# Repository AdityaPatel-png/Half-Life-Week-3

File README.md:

# Half-Life-Week-3
Miniature synthesizer project
For this project, I have decided to make a miniature synthesizer powered by a Raspberry Pi Zero.
It will have 13 keys (1 octave) and a dial that will allow to change between 4 octaves.
The code will be done in arduino and the design in Kicad.
I am not a musician and therefore will use a friend to test its functionality in the build week.

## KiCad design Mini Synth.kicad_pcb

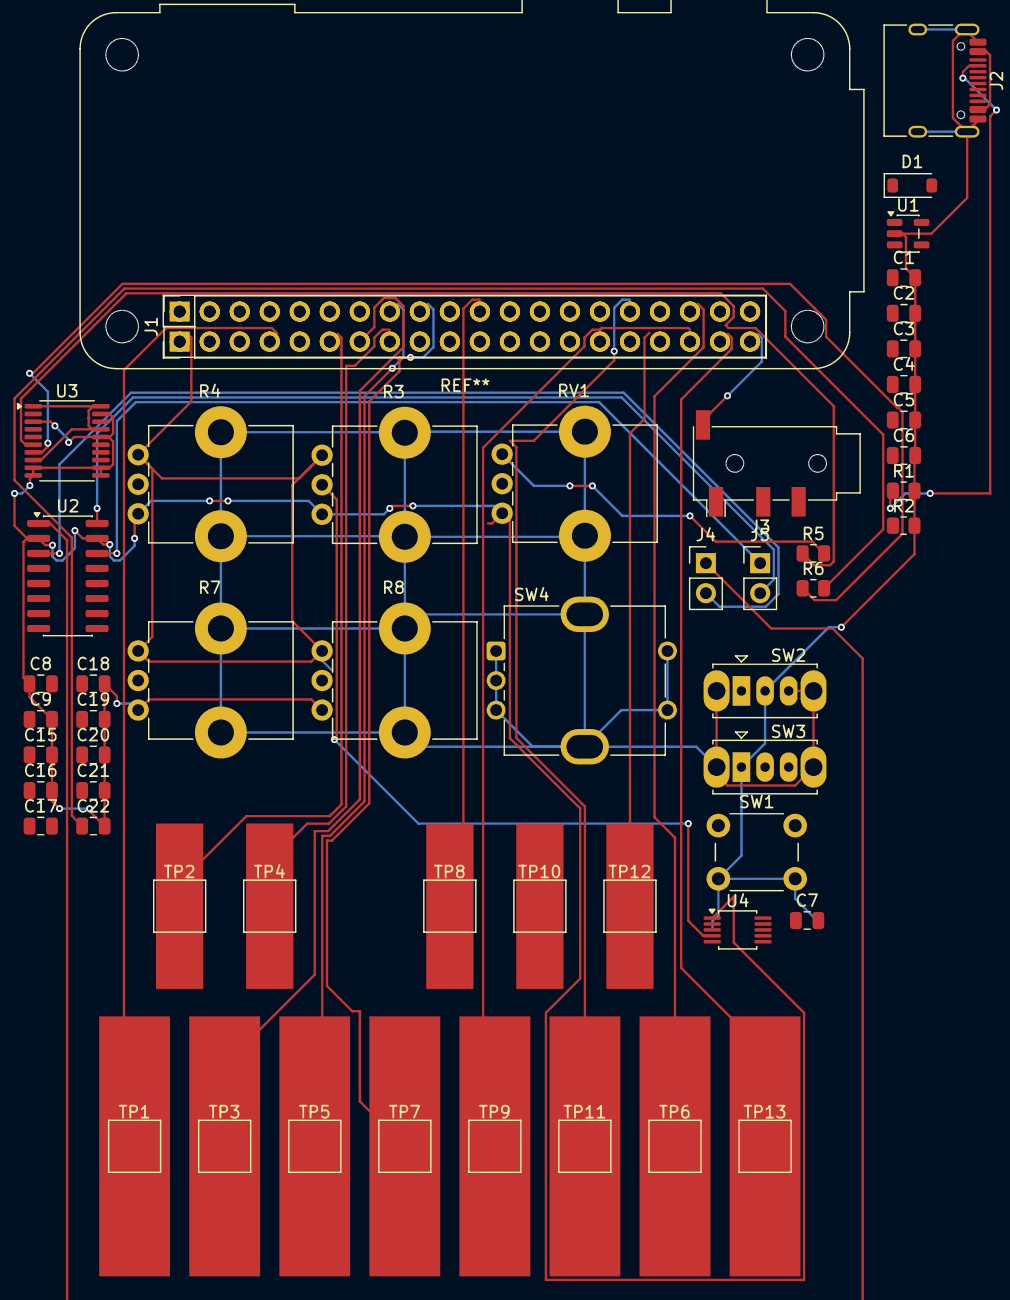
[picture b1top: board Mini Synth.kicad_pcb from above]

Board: 2 copper layers, 53 parts (0 on the bottom side), 47 nets.

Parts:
C1: 10µF; C_0805_2012Metric
C2, C3, C17, C19, C20: 1.0µF; C_0805_2012Metric
C4, C5, C6, C7, C15, C16, C18: 0.1µF; C_0805_2012Metric
C8, C9: C; C_0805_2012Metric
C21, C22: 2.2nF; C_0805_2012Metric
D1: D_Schottky; D_SOD-123
J1: Conn_02x20_Odd_Even; PinHeader_2x20_P2.54mm_Vertical
J2: USB_C_Receptacle_USB2.0_16P; USB_C_Receptacle_HRO_TYPE-C-31-M-12
J3: AudioJack3_Switch; Jack_3.5mm_PJ320D_Horizontal
J4, J5: Conn_01x02_Socket; PinHeader_1x02_P2.54mm_Vertical
R1, R2: 5.1K; R_0805_2012Metric
R3, R4, R7, R8: Potentiometer; Potentiometer_Bourns_PTV09A-1_Single_Vertical
R5, R6: 470; R_0805_2012Metric
RV1: R_Potentiometer_Dual; Potentiometer_Bourns_PTV09A-1_Single_Vertical
SW1: SW_Push; SW_PUSH_6mm
SW2: SW_SPST; SW_Slide_SPDT_Straight_CK_OS102011MS2Q
SW3: SW_Slide_DPDT; SW_Slide_SPDT_Straight_CK_OS102011MS2Q
SW4: SW_Rotary_1x4_MP; RotaryEncoder_Bourns_Vertical_PEC12R-3x17F-Sxxxx
TP1: KEY_C; TestPoint_Pad_4.0x4.0mm
TP2: KEY_CSHARP; TestPoint_Pad_4.0x4.0mm
TP3: KEY_D; TestPoint_Pad_4.0x4.0mm
TP4: KEY_DSHARP; TestPoint_Pad_4.0x4.0mm
TP5: KEY_E; TestPoint_Pad_4.0x4.0mm
TP6: KEY_B; TestPoint_Pad_4.0x4.0mm
TP7: KEY_F; TestPoint_Pad_4.0x4.0mm
TP8: KEY_FSHARP; TestPoint_Pad_4.0x4.0mm
TP9: KEY_G; TestPoint_Pad_4.0x4.0mm
TP10: KEY_GSHARP; TestPoint_Pad_4.0x4.0mm
TP11: KEY_A; TestPoint_Pad_4.0x4.0mm
TP12: KEY_ASHARP; TestPoint_Pad_4.0x4.0mm
TP13: KEY_HIGH_C; TestPoint_Pad_4.0x4.0mm
U1: TLV75533PDBV; SOT-23-5
U2: PAM8403D; SOIC-16_3.9x9.9mm_P1.27mm
U3: PCM5102A; TSSOP-20_4.4x6.5mm_P0.65mm
U4: ADS1115IDGS; TSSOP-10_3x3mm_P0.5mm

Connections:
/3V3_ANA: C3.1, C5.1
/5V_SYS: C1.1, C2.1, C4.1, C6.1, D1.2 (A), U1.1 (IN), U1.3 (EN)
/Audio DAC/3V3_ANA: C15.1, C16.1, C18.1, U1.5 (OUT), U3.1 (CPVDD), U3.8 (AVDD), U3.17 (XSMT), U3.20 (DVDD)
/Audio DAC/5V_SYS: C9.1, J1.2, U2.4 (PVDD), U2.5 (~MUTE), U2.6 (VDD), U2.12 (~SHDN), U2.13 (PVDD)
/Audio DAC/AUDIO_L: C21.1, R5.2, RV1.3
/Audio DAC/AUDIO_R: C22.1, R6.2
/Audio DAC/I2S_BCK: J1.12, U3.13 (BCK)
/Audio DAC/I2S_DOUT: J1.40, U3.14 (DIN)
/Audio DAC/I2S_LRCK: J1.29, J1.35, TP9.1 (1_1), U3.15 (LRCK)
/Controls/3V3_DIG: C7.1, J1.1, R3.3, R4.3, R7.3, R8.3, U4.8 (VDD)
/Controls/I2C_SCL: J1.5, U4.10 (SCL)
/Controls/I2C_SDA: J1.3, U4.9 (SDA)
/Controls/SW_ARP: J1.24, SW2.1 (A)
/Controls/SW_GLIDE: J1.23, SW3.2 (B)
/Controls/SW_WAVE: J1.21, SW1.1
/Keyboard/KEY_A: J1.32, TP11.1 (1_1)
/Keyboard/KEY_ASHARP: J1.33, TP12.1 (1_1)
/Keyboard/KEY_B: J1.36, TP6.1 (1_1)
/Keyboard/KEY_C: J1.7, TP1.1 (1_1)
/Keyboard/KEY_CSHARP: J1.11, TP2.1 (1_1)
/Keyboard/KEY_D: J1.13, TP3.1 (1_1)
/Keyboard/KEY_DSHARP: J1.15, TP4.1 (1_1)
/Keyboard/KEY_E: J1.16, TP5.1 (1_1)
/Keyboard/KEY_F: J1.18, TP7.1 (1_1)
/Keyboard/KEY_FSHARP: J1.22, TP8.1 (1_1)
/Keyboard/KEY_GSHARP: J1.31, TP10.1 (1_1)
/Keyboard/KEY_HIGH_C: J1.37, TP13.1 (1_1)
GND: C1.2, C2.2, C3.2, C4.2, C5.2, C6.2, C7.2, C8.1, C9.2, C15.2, C16.2, C18.2, C19.2, C20.2, C21.2, C22.2, J1.6, J1.9, J1.14, J1.20, J1.25, J1.30, J1.34, J1.39, J2.A1 (GND), J2.A12 (GND), J2.B1 (GND), J2.B12 (GND), J2.SH (SHIELD), J3.S, R1.2, R2.2, R3.1, R4.1, R7.1, R8.1, RV1.1, SW1.2, SW2.2 (B), SW3.1 (A), U1.2 (GND), U2.2 (PGND), U2.11 (GND), U2.15 (PGND), U3.3 (CPGND), U3.9 (AGND), U3.10 (DEMP), U3.11 (FLT), U3.12 (SCK), U3.16 (FMT), U3.19 (DGND), U4.1 (ADDR), U4.3 (GND)
unnamed: D1.1 (K), J2.A4 (VBUS), J2.A9 (VBUS), J2.B4 (VBUS), J2.B9 (VBUS)
unnamed: J2.A5 (CC1), R1.1
unnamed: J2.B5 (CC2), R2.1
unnamed: J3.T, RV1.2
unnamed: J4.1, U2.1 (LOUT+)
unnamed: J4.2, U2.3 (LOUT-)
unnamed: J5.1, U2.14 (ROUT-)
unnamed: J5.2, U2.16 (ROUT+)
unnamed: C8.2, U2.8 (VREF)
unnamed: C17.1, U3.4 (CAPM)
unnamed: C17.2, U3.2 (CAPP)
unnamed: C19.1, U3.18 (LDOO)
unnamed: R5.1, U3.6 (OUTL)
unnamed: R6.1, U3.7 (OUTR)
unnamed: C20.1, U3.5 (VNEG)
unnamed: R3.2, U4.4 (AIN0)
unnamed: R4.2, U4.5 (AIN1)
unnamed: R7.2, U4.6 (AIN2)
unnamed: R8.2, U4.7 (AIN3)

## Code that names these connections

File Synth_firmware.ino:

/* code for synthsizer project
this project will be a mini synthesier, with 13 keys. (8 white 5 black)
it will run using a rapsberry Pi zero and hopefully work independently of an external device.
it will also have dials for volume, octave, and other features that modify its sound.
it will be able to freely switch between headphone and usage of built in speakers
*/
#include <Wire.h>
#include <Adafruit_ADS1015.h>

const int KEY_C       = 4;   // Note C
const int KEY_CSHARP  = 17;  // Note C#
const int KEY_D       = 27;  // Note D
const int KEY_DSHARP  = 22;  // Note D#
const int KEY_E       = 23;  // Note E
const int KEY_F       = 24;  // Note F
const int KEY_FSHARP  = 25;  // Note F#
const int KEY_G       = 5;   // Note G
const int KEY_GSHARP  = 6;   // Note G#
const int KEY_A       = 12;  // Note A
const int KEY_ASHARP  = 13;  // Note A#
const int KEY_B       = 16;  // Note B
const int KEY_HIGH_C  = 26;  // Note High C

const int PIN_SW_WAVE  = 9;   // Wave
const int PIN_SW_GLIDE = 11;  // Glide
const int PIN_SW_ARP   = 8;   // Arp
const int OCT_1 = 14; 
const int OCT_2 = 15;
const int OCT_3 = 0;
const int OCT_4 = 1;

const float NOTE_FREQS[13] = {
    261.63, // C
    277.18, // C#
    293.66, // D
    311.13, // D#
    329.63, // E
    349.23, // F
    369.99, // F#
    392.00, // G
    415.30, // G#
    440.00, // A
    466.16, // A#
    493.88, // B
    523.25  // High C
};

const int KEY_PINS[13] = {KEY_C, KEY_CSHARP, KEY_D, KEY_DSHARP, KEY_E, KEY_F, KEY_FSHARP, KEY_G, KEY_GSHARP, KEY_A, KEY_ASHARP, KEY_B, KEY_HIGH_C};
const int OCT_PINS[4]  = {OCT_1, OCT_2, OCT_3, OCT_4};

Adafruit_ADS1115 ads;

float currentFreq = 0.0;
float targetFreq = 0.0;
float phase = 0.0;
unsigned long lastSampleTime = 0;

int waveformType = 0;   
bool glideEnabled = false;
float glideSpeed = 0.08;  
float filterCutoff = 0.5;
float filterLastVal = 0.0;

bool lastButtonState = HIGH; 

void setup() {
    Wire.begin();
    
    for (int i = 0; i < 13; i++) {
        pinMode(KEY_PINS[i], INPUT_PULLUP);
    }
    
    pinMode(PIN_SW_WAVE, INPUT_PULLUP);
    pinMode(PIN_SW_GLIDE, INPUT_PULLUP);
    pinMode(PIN_SW_ARP, INPUT_PULLUP);
    
    for (int i = 0; i < 4; i++) {
        pinMode(OCT_PINS[i], INPUT_PULLUP);
    }

    ads.begin();
    ads.setGain(GAIN_ONE); 
    
    lastSampleTime = micros();
}

void loop() {

    float octaveMultiplier = 1.0;
    if (digitalRead(OCT_1) == LOW) octaveMultiplier = 0.25; /
    else if (digitalRead(OCT_2) == LOW) octaveMultiplier = 0.5;  
    else if (digitalRead(OCT_3) == LOW) octaveMultiplier = 1.0;  
    else if (digitalRead(OCT_4) == LOW) octaveMultiplier = 2.0; 

    uint16_t adc0 = ads.readADC_SingleEnded(0);
    filterCutoff = (float)adc0 / 32768.0; 
    if (filterCutoff < 0.01) filterCutoff = 0.01; 

    glideEnabled = (digitalRead(PIN_SW_GLIDE) == LOW);

    bool currentButtonState = digitalRead(PIN_SW_WAVE);
    if (currentButtonState == LOW && lastButtonState == HIGH) {
        waveformType = (waveformType + 1) % 3; 
        delay(150); 
    }
    lastButtonState = currentButtonState;

    float triggeredFreq = 0.0;
    bool notePressedThisCycle = false;

    for (int i = 0; i < 13; i++) {
        if (digitalRead(KEY_PINS[i]) == LOW) {
            triggeredFreq = NOTE_FREQS[i] * octaveMultiplier;
            notePressedThisCycle = true;
            break; 
        }
    }

    if (notePressedThisCycle) {
        targetFreq = triggeredFreq;
    } else {
        if (!glideEnabled) targetFreq = 0.0;
    }

    if (glideEnabled && notePressedThisCycle) {
        currentFreq += (targetFreq - currentFreq) * glideSpeed;
    } else {
        currentFreq = targetFreq;
    }

    if (currentFreq > 0.0 && (notePressedThisCycle || (glideEnabled && currentFreq > 1.0))) {
        unsigned long currentMicros = micros();
        float deltaTime = (float)(currentMicros - lastSampleTime) / 1000000.0;
        lastSampleTime = currentMicros;

        phase += 2.0 * PI * currentFreq * deltaTime;
        if (phase >= 2.0 * PI) phase -= 2.0 * PI;

        float rawSample = 0.0;

        if (waveformType == 0) {      
            rawSample = 1.0 - (2.0 * (phase / (2.0 * PI)));
        } else if (waveformType == 1) {
            rawSample = (phase < PI) ? 1.0 : -1.0;
        } else {                 
            rawSample = 2.0 * abs(2.0 * (phase / (2.0 * PI)) - 1.0) - 1.0;
        }

        float filteredSample = filterLastVal + filterCutoff * (rawSample - filterLastVal);
        filterLastVal = filteredSample;

    } else {
        lastSampleTime = micros(); 
    }

    delayMicroseconds(50);
}
